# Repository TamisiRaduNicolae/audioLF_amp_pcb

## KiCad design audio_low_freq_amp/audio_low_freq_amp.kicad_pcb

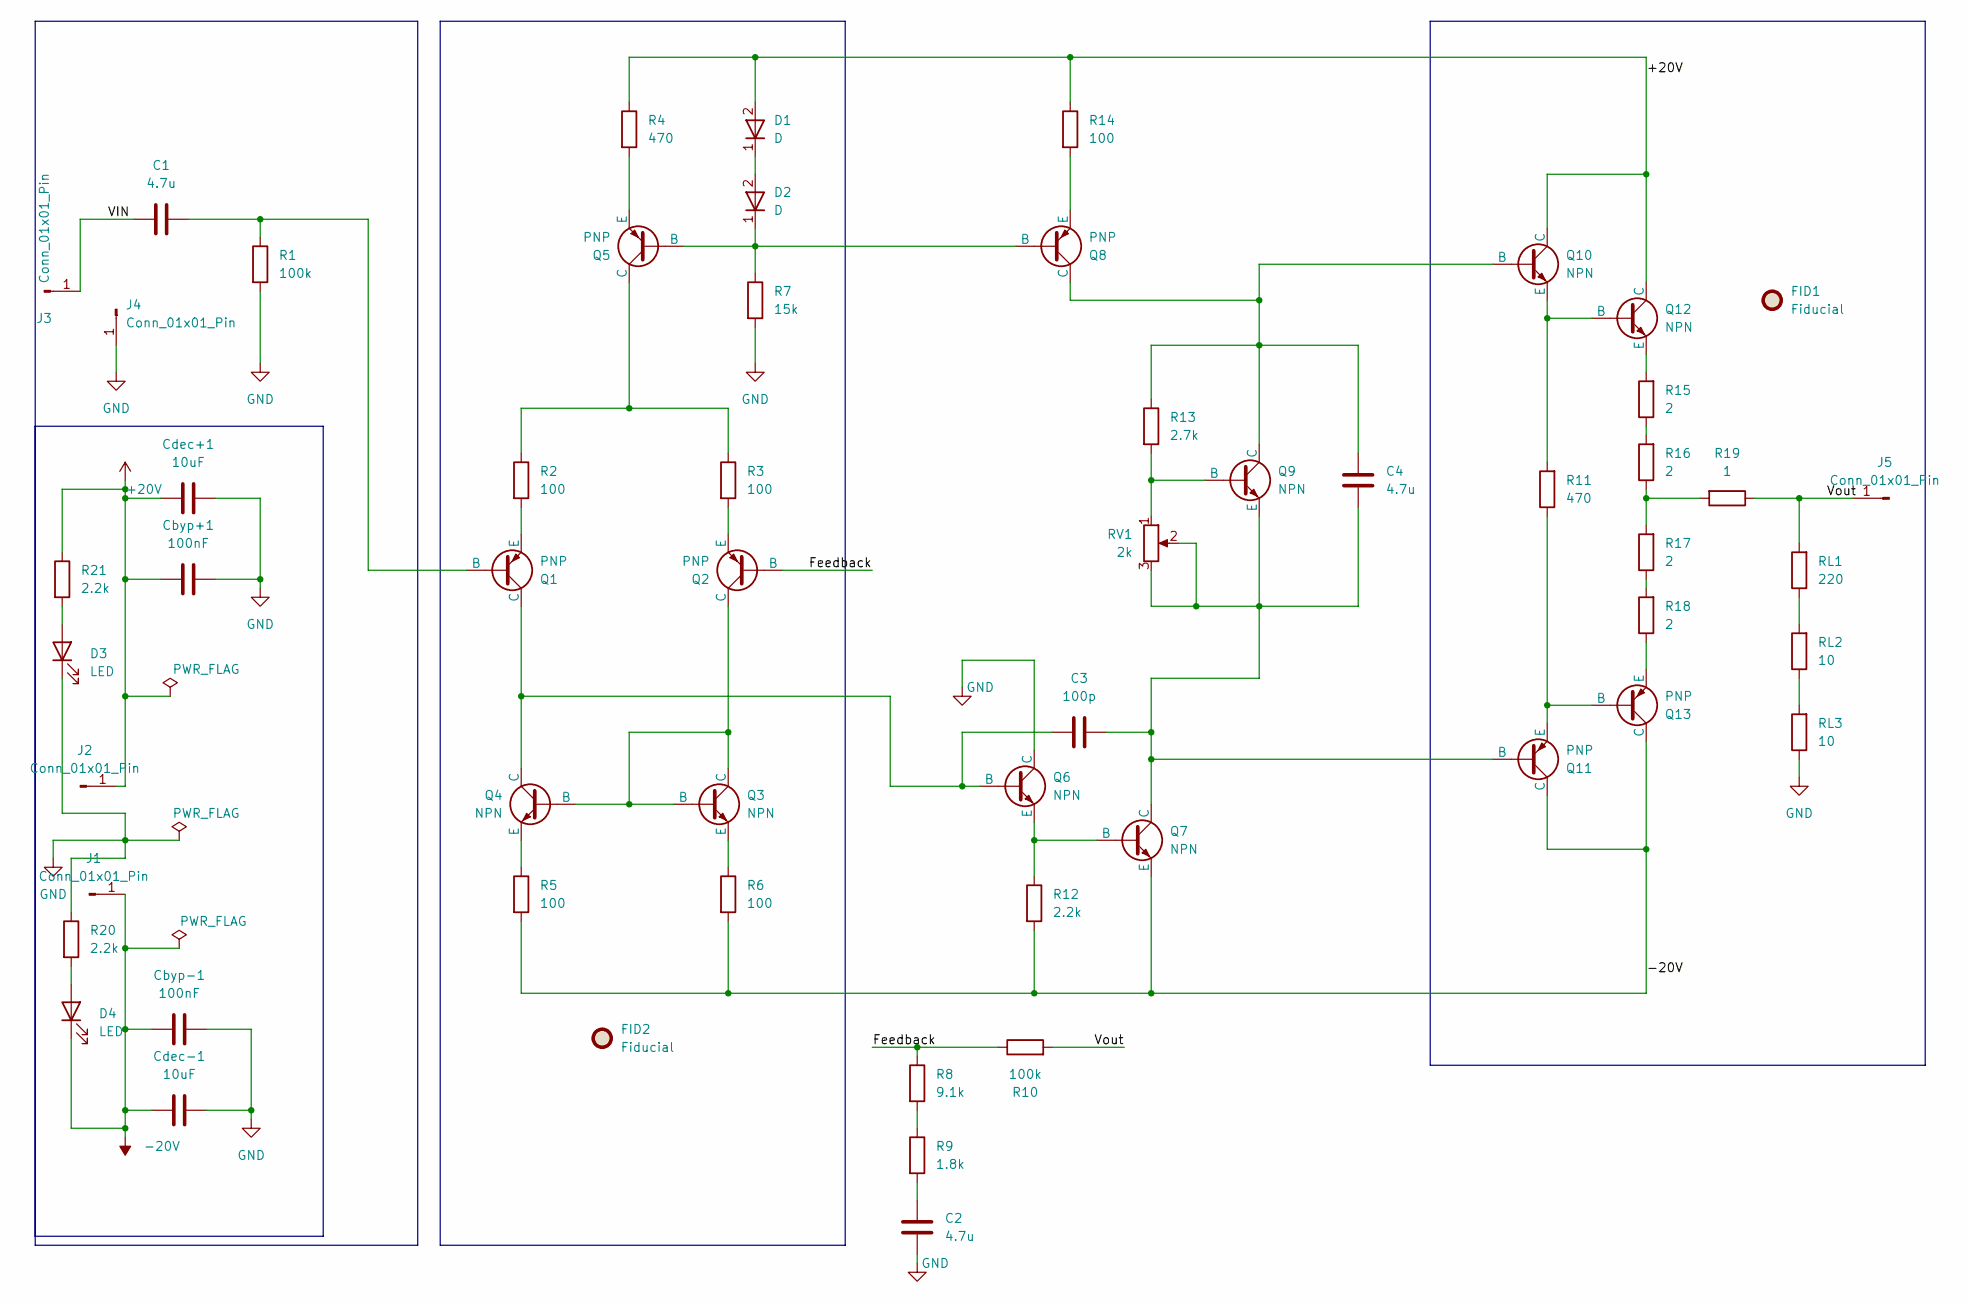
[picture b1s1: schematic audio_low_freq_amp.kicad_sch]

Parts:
C1, C2, C4: 4.7u; C_0805_2012Metric
C3: 100p; C_0805_2012Metric
Cbyp+1: 100nF; C_0805_2012Metric
Cbyp-1: 100nF; C_0805_2012Metric
Cdec+1: 10uF; 10uF_smd_6.3x5.4_Radu
Cdec-1: 10uF; 10uF_smd_6.3x5.4_Radu
D1, D2: D; D_0805_2012Metric
D3, D4: LED; LED_0805_2012Metric
FID1, FID2: Fiducial; Fiducial_1mm_Mask2mm
J1, J2, J3, J4, J5: Conn_01x01_Pin; J_conn_4x4mm_Radu
Q1, Q2, Q5, Q8, Q11, Q13: PNP; sot23_Radu
Q3, Q4, Q6, Q7, Q9, Q10, Q12: NPN; sot23_Radu
R1, R10: 100k; R_0805_2012Metric
R2, R3, R5, R6, R14: 100; R_0805_2012Metric
R4, R11: 470; R_0805_2012Metric
R7: 15k; R_0805_2012Metric
R8: 9.1k; R_0805_2012Metric
R9: 1.8k; R_0805_2012Metric
R12, R20, R21: 2.2k; R_0805_2012Metric
R13: 2.7k; R_0805_2012Metric
R15, R16, R17, R18: 2; R_0805_2012Metric
R19: 1; R_0805_2012Metric
RL1: 220; R_0805_2012Metric
RL2, RL3: 10; R_0805_2012Metric
RV1: 2k; ts53yl_Radu

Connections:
+20V: Cbyp+1.1, Cdec+1.1, D1.2 (A), J2.1, Q10.1 (C), Q12.1 (C), R4.1, R14.1, R21.1; also elsewhere on the board
-20V: Cbyp-1.1, Cdec-1.2, D4.1 (K), J1.1, Q7.3 (E), Q11.1 (C), Q13.1 (C), R5.2, R6.2, R12.2; also elsewhere on the board
/Feedback: Q2.2 (B), R8.1, R10.1
/VIN: C1.1, J3.1; also elsewhere on the board
/Vout: J5.1, R10.2, R19.1, RL1.2; also elsewhere on the board
GND: C2.1, Cbyp+1.2, Cbyp-1.2, Cdec+1.2, Cdec-1.1, D3.1 (K), J4.1, Q6.1 (C), R1.2, R7.2, R20.1, RL3.1; also elsewhere on the board
unnamed: C2.2, R9.2
unnamed: D1.1 (K), D2.2 (A)
unnamed: D2.1 (K), Q5.2 (B), Q8.2 (B), R7.1
unnamed: D3.2 (A), R21.2
unnamed: D4.2 (A), R20.2
unnamed: C1.2, Q1.2 (B), R1.1
unnamed: C3.1, Q1.1 (C), Q4.1 (C), Q6.2 (B)
unnamed: Q1.3 (E), R2.2
unnamed: Q2.1 (C), Q3.1 (C), Q3.2 (B), Q4.2 (B)
unnamed: Q2.3 (E), R3.2
unnamed: Q3.3 (E), R6.1
unnamed: Q4.3 (E), R5.1
unnamed: Q5.1 (C), R2.1, R3.1
unnamed: Q5.3 (E), R4.2
unnamed: Q6.3 (E), Q7.2 (B), R12.1
unnamed: Q8.3 (E), R14.2
unnamed: Q9.2 (B), R13.2, RV1.1
unnamed: C4.2, Q8.1 (C), Q9.1 (C), Q10.2 (B), R13.1
unnamed: Q10.3 (E), Q12.2 (B), R11.2
unnamed: C3.2, C4.1, Q7.1 (C), Q9.3 (E), Q11.2 (B), RV1.2, RV1.3
unnamed: Q11.3 (E), Q13.2 (B), R11.1
unnamed: Q12.3 (E), R15.2
unnamed: Q13.3 (E), R18.1
unnamed: R8.2, R9.1
unnamed: R15.1, R16.2
unnamed: R16.1, R17.2, R19.2
unnamed: R17.1, R18.2
unnamed: RL1.1, RL2.2
unnamed: RL2.1, RL3.2

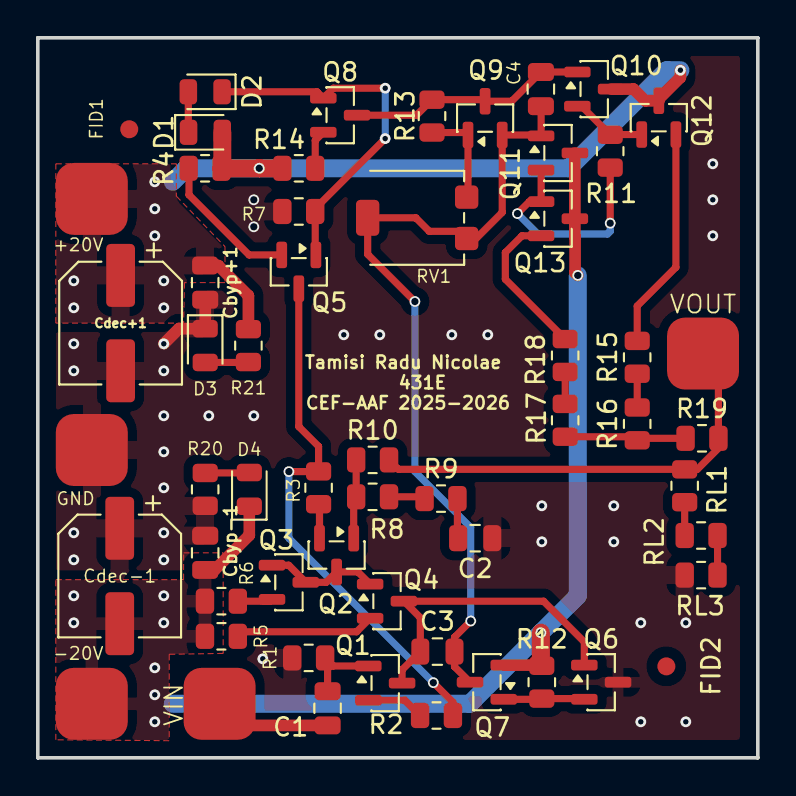
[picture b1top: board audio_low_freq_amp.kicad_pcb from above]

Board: 2 copper layers, 40.0 x 40.0 mm, 57 parts (0 on the bottom side), 35 nets.

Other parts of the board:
+20V: Conn_01x01_Pin; J_conn_4x4mm_Radu
-20V: Conn_01x01_Pin; J_conn_4x4mm_Radu
GND: Conn_01x01_Pin; J_conn_4x4mm_Radu
VIN: Conn_01x01_Pin; J_conn_4x4mm_Radu
VOUT: Conn_01x01_Pin; J_conn_4x4mm_Radu

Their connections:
+20V: +20V.1; also elsewhere on the board
-20V: -20V.1; also elsewhere on the board
/VIN: VIN.1; also elsewhere on the board
/Vout: VOUT.1; also elsewhere on the board
GND: GND.1; also elsewhere on the board

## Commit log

2025-10-20 created the schematicin kicad 9 and placed power and signal sources
2025-10-22 finished unrefined version of the schematic with a new approach in mind. works very good for beginning, but needs more work. great place to start bc we almost got a sine wave at output and gain is a 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
2025-10-29 commit before going to check up with the professor
2025-11-08 added a tina ti design which is new and more stable in freq and temp, inspired by small signal audio amp book by douglas self
2025-11-10 did some tweaks and finalized the version before going to present. have 71 degrees of phase margin and just 14 uV of output offset
2025-11-23 modified final sch in tina and kicad
2025-11-29 added constraints to pcb and did some custom footprints
2025-11-30 layed out the parts on pcb, next is routing
2025-11-30 made some placing adjustments. should be ready for first routing stage
2025-11-30 finished first iteration of routing
2025-12-07 moved fiducial fid2 to be diagonally oposed with the first and made adjustments to traces and pours
2025-12-07 found some unconnected traces and resolved; still have some insignificant errors (2) about not having minimum 2 spokes for thermal relief
